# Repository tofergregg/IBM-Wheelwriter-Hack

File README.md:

# IBM-Wheelwriter-Hack
Turning an IBM Wheelwriter into a unique printer

Video:<br>

This project has three goals:

1. Electronically connect an Arduino to an IBM Wheelwriter 6 (will probably work for other models) to emulate the IBM printer option card when using a custom driver.
2. Allow someone to type directly to the typewriter from a computer keyboard, through a computer.
3. Add fun options, e.g., raster printing (!) at a low dpi through the use of micro-up/down and micro-backspace.

## Background
The IBM Wheelwriter, circa 1984, is an electronic typewriter with a beautiful Model M keyboard and a daisy-wheel print head. The typewriter is (not suprisingly, given that it is an IBM) built like a tank, and the PCBs are exceedingly well laid out and annotated, and easy to access. The case pops off with a bit of elbow grease, and there is an expansion port on one of the two PCBs with labeled pins. Yay!

## Technical Details
The only pins we really care about are "bus" and ground, although eventually we'll care about 5V when we attach the Arduino and want to power it from the typewriter itself.

Reverse-engineering the bus has been an interesting two-week endeavor. The tools necessary: an Arduino (I'm using a Light Blue Bean+ (Update on 17 Jan 2017: I have added code for an ATmega Arduino Nano) and a logic analyzer. The initial logic analyzer I used was a Bus Pirate, but unfortunately the BP does not have enough memory to capture some of the longer sequences of commands (e.g., a carriage return). So, a colleague loaned me a Saleae 8-pin logic analyzer, which has worked great (though it does have some quirks).

As of February 2017, I have successfully reverse engineered printing characters, carriage returns, fast printing of characters, print head forwards/backwards/up/down, etc. Here is the basic idea for sending a command on the bus:

* Pulse period: 5.34us (I originally thought it was a 5.25us pulse, but after locating the 11.975MHz crystal on the PCB, I realized that 11.975MHz divided by 64 is 5.34us, which is most likely the actual period. In all of my testing I assumed it was 5.25us, and it worked fine.
* Number of pulses sent per command: 10 (an "I'm writing to the bus" to begin, and nine more bits)
* Normal state of the bus: high (5V), and devices sending commands must pull the bus to low for a zero, and leave high for a one.
* The first pulse is always a throwaway 0, indicating that a device is going to write 9 more bits to the bus.
* The next nine bits are (as far as I can tell) in LSB order. Commands seem to always start with 0b100100001 (which is sent right-most bit first). I originally thought the commands were MSB first, but when I was reverse engineering the carriage-return command the numbers came out such that it looks like it is LSB. This makes reading the logic traces in the reverse order from the numeric bit pattern. Maybe I should have kept the MSB ordering in the code because it is easier for humans to read, but I switched it to make it consistent with the way the typewriter expects commands.
* When a device sends its 10 bits on the bus, there is almost always a response from the motor driver PCB (that's what I'm calling it), and this response is usually a 10-byte zero (a 53.4us zero pulse, basically). We need to look for this response before sending the next 10-bit value in our command.
* The reason I am somewhat hesitant to declare the MSB/LSB debate finished is because the character table is completely whacky. It is not ASCII, and it isn't any of the EBCDIC variations I've tracked down. You might think that there would be some method to it, but I haven't yet figured it out. The table below is what I have so far; as you can see, the characters A, B, C have character codes 0x20, 0x12, and 0x1b. I have a feeling that the codes might be based off of the keyboard scan codes, but I haven't found the pattern yet.

* The following is the Arduino array mapping ASCII to the characters the printer expects.
I haven't figured out what encoding the typewriter expects, and capturing this data was
an exercise in patience and a lot of "type a key, look at the bit pattern" (which I
automated to every extent possible!). Note: this is the mapping for the __Prestige Elite 12P__
daisy wheel -- I will eventually get a Courier printwheel to see what characters need to be
modified (e.g., there are no curly braces in the Prestige Elite font).

<pre>
int asciiTrans[128] = 
//col: 0     1     2     3     4     5     6     7     8     9     a     b     c     d     e     f     row:
    {0x00, 0x00, 0x00, 0x00, 0x00, 0x00, 0x00, 0x00, 0x00, 0x00, 0x00, 0x00, 0x00, 0x00, 0x00, 0x00, // 0

//    
     0x00, 0x00, 0x00, 0x00, 0x00, 0x00, 0x00, 0x00, 0x00, 0x00, 0x00, 0x00, 0x00, 0x00, 0x00, 0x00, // 1
     
//    sp     !     "     #     $     %     &     '     (     )     *     +     ,     -     .     /
     0x00, 0x49, 0x4b, 0x38, 0x37, 0x39, 0x3f, 0x4c, 0x23, 0x16, 0x36, 0x3b, 0xc, 0x0e, 0x57, 0x28, // 2
     
//     0     1     2     3     4     5     6     7     8     9     :     ;     <     =     >     ?
     0x30, 0x2e, 0x2f, 0x2c, 0x32, 0x31, 0x33, 0x35, 0x34, 0x2a ,0x4e, 0x50, 0x00, 0x4d, 0x00, 0x4a, // 3

//     @     A     B     C     D     E     F     G     H     I     J     K     L     M     N     O
     0x3d, 0x20, 0x12, 0x1b, 0x1d, 0x1e, 0x11, 0x0f, 0x14, 0x1F, 0x21, 0x2b, 0x18, 0x24, 0x1a, 0x22, // 4

//     P     Q     R     S     T     U     V     W     X     Y     Z     [     \     ]     ^     _
     0x15, 0x3e, 0x17, 0x19, 0x1c, 0x10, 0x0d, 0x29, 0x2d, 0x26, 0x13, 0x41, 0x00, 0x40, 0x00, 0x4f, // 5
     
//     `     a     b     c     d     e     f     g     h     i     j     k     l     m     n     o
     0x00, 0x01, 0x59, 0x05, 0x07, 0x60, 0x0a, 0x5a, 0x08, 0x5d, 0x56, 0x0b, 0x09, 0x04, 0x02, 0x5f, // 6
     
//     p     q     r     s     t     u     v     w     x     y     z     {     |     }     ~    DEL
     0x5c, 0x52, 0x03, 0x06, 0x5e, 0x5b, 0x53, 0x55, 0x51, 0x58, 0x54, 0x00, 0x00, 0x00, 0x00, 0x00}; // 7
</pre>

To send commands to the typewriter, we connect one pin of the Arduino to the bus through a MOSFET transistor (see the breadboard layout below, or the schematic in the
KiCad files). When we set this pin high, the bus is pulled low, indicating a zero that we want to send. We capture other devices commands with a different Arduino pin that reads the raw state of the bus.

The hardest part about making the commands work is that there isn't a clock on the bus, and all commands must be timed for as close to 5.34us pulses as we can get. The Arduino is *just* barely fast enough to do this, and you have to resort to directly writing to the `PORTD` (or `PORTB`) pin registers and reading from the `PIND` (or `PINB`) registers to hit the tolerances. I.e., you can't use `digitalWrite()` or `digitalRead()` -- the commands are just too slow. The highest granularity timer we have access to on the Arduino (without going super-duper low-level) is `delayMicroseconds()`, which can come close enough to 5.34us to work, but it takes a bit of fiddling to get right. I will eventually port the code to an Arduino proper, but on the Light Blue Bean+, the tolerances don't have any wiggle room. Side note: the LBB+ has some internal ports rearranged, so `PORTD` and `PORTB` do not map to the standard Arduino pins. I've noted that in the code where necessary, and the code for the Arduino Nano has slightly different pins: pin 2 is the bus trigger through the MOSFET, and pin 3 is the bus input. Pin 4 is currently used as a button for testing.  

## Graphics
This has been one of the most fun parts of the project. I realized early on during my analysis of the 
signals coming from the bus that the typewriter has the ability to advance the print head in very small increments,
both horizontally and vertically. This led to the idea that I could basically turn the typewriter 
into a slow, low-resolution dot-matrix printer by utilizing the period key as a pixel, and printing out runs of 
dots and spaces to form images.

My initial attempts involved simply breaking an image down into a grid of black-and-white pixels,
and then sending each black pixel as a period, and each white pixel as a space. This worked, but was
exceedingly slow (as you can imagine). For the second iteration, I re-wrote the encoding algorithm to 
accept a [run-length-encoded](https://en.wikipedia.org/wiki/Run-length_encoding) string of periods and
spaces, allowing me to fast-print the runs, which sped up the process considerbly. In the current
iteration, I have updated the Arduino code to print runs of periods (as before), but also to simply
advance the print head an equivalent number of spaces for whitespace, instead of individually
advancing one space at a time (which sounded cool, but was slow...)

At this point, the graphics printing code on the Arduino is stable, but I'm still trying to
figure out the best way to scale images so they make sense in black and white when
printed at (roughly) 50-dots per inch. As I write more of the front-end software, I imagine
I will re-invent the wheel some more and land on a reasonable method.

Here is an example of what the graphics looks like:

## Bold, underline, and other non-standard functions
Interstingly, the Wheelwriter 6 that I have does not have bold functionality, 
though it does have a built-in underline function. Not suprisingly, an underline
is as simple as writing a character then immediately writing the underline character,
before advancing the print head. I have manually implemented this instead of attempting
to turn on the built-in underline functionality.

Bold is a bit more interesting: because this model does not have a bold function, I
had to play around with what bold should look like. It turns out that the best bold
I have been able to create works like this:

1. print a character
2. advance the print head one micro-space
3. reprint the character
4. advance the print head a full character space less one microspace (to keep the spacing intact).

I think the bold looks great. :)

If anyone has any ideas on how to get the daisy wheel to print at an angle, let
me know so I can implement italics. (/joke)  

For the `sendToNano.py` program, I have included a parser that
looks for "**" (bold) and "__" (underline) Markdown and sends the appropriate commands
to the typewriter to format text in this fashion.

Here is a picture of the output with formatted text:

## Breadboard Layout
The circuit used to connect the typewriter to an Arduino is extremely simple. 

## Nano Shield PCB

See the KiCad files for full schematic ([hardware/Arduino_NanoShield folder](hardware/Arduino_NanoShield)) of a Nano shield,
or order the part directly from OSH Park (under $6 for three copies):

<a href="https://oshpark.com/shared_projects/HWk60tsg"></img></a>

(Note: you will need two surface-mount components for the shield: a 
[200&#8486; 1206 resistor ($0.10 at Digikey)](http://www.digikey.com/product-detail/en/yageo/RC1206JR-07200RL/311-200ERCT-ND/732194)
(and anything in the 200&#8486; range should work), 
and an [n-channel MOSFET (2N7002 works fine) in an SOT-23 package, ($0.14 at Digikey)](http://www.digikey.com/product-detail/en/on-semiconductor/2N7002LT1G/2N7002LT1GOSCT-ND/917791)).
If you want a proper connector for the typewriter interface, [you can get one, too ($0.56 at DigiKey)](https://www.digikey.com/product-detail/en/molex-connector-corporation/0050579310/WM5289-ND/2731451)

Note: you do __not__ need to connect the 5V to the typewriter (indeed, do not, or you risk electrical issues);
I put that onto the board in case someone did not want to connect the Arduino through USB. But, USB is how
the computer controls the typewriter, so it will be connected...

Of course, you also need to be
able to [solder surface mount components](https://www.sparkfun.com/tutorials/category/2).

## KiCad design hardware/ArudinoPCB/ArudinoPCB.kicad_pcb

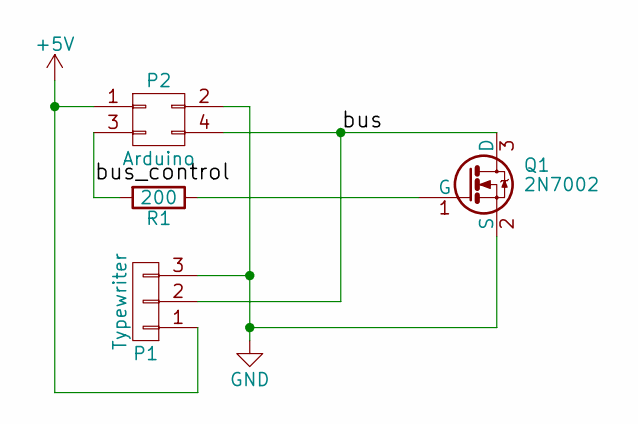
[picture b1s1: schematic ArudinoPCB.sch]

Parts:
P1: Typewriter; Socket_Strip_Straight_1x03
P2: Arduino; Socket_Strip_Straight_2x02
Q1: 2N7002; SOT-23
R1: 200; R_1206

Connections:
+5V: P1.1, P2.1
GND: P1.3, P2.2, Q1.2 (S)
unnamed: P1.2, P2.4, Q1.3 (D)
unnamed: P2.3, R1.2
unnamed: Q1.1 (G), R1.1

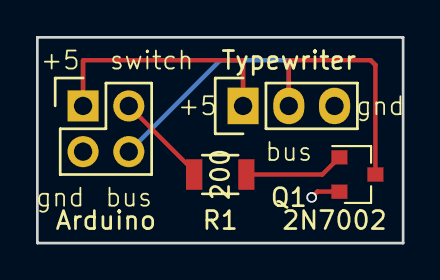
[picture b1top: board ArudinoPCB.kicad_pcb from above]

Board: 2 copper layers, 20.3 x 11.4 mm, 4 parts (0 on the bottom side), 5 nets.

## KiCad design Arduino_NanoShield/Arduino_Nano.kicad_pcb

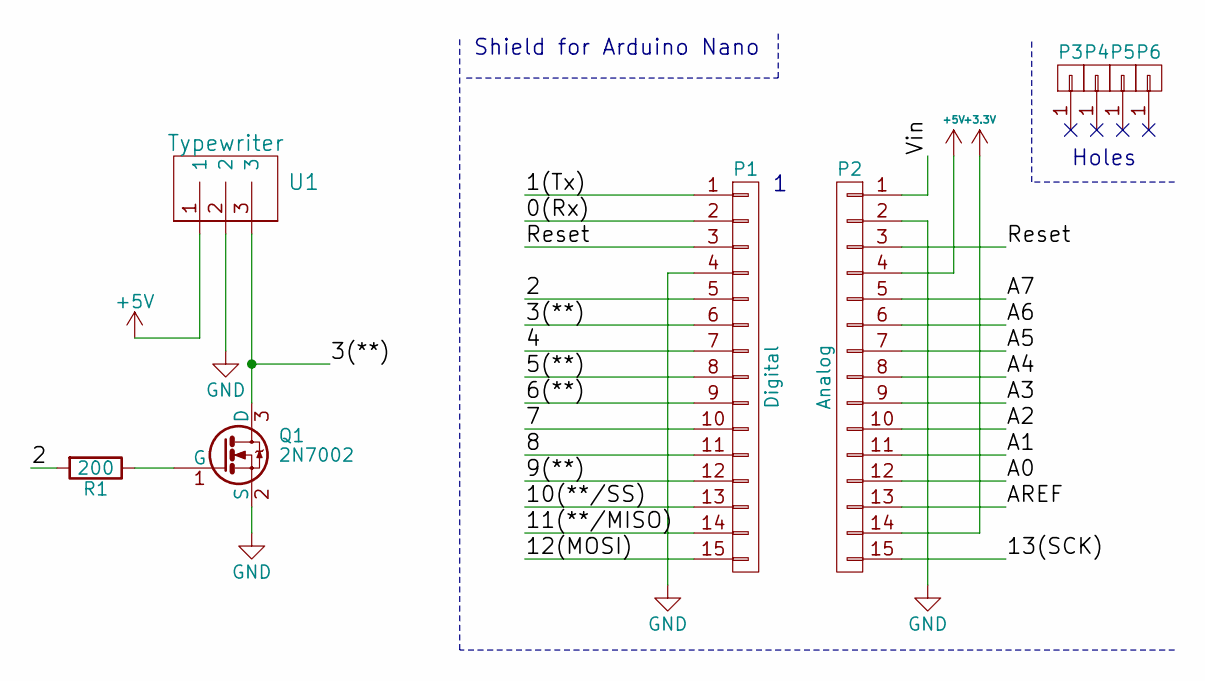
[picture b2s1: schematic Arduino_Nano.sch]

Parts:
P1: Digital; Socket_Strip_Arduino_1x15
P2: Analog; Socket_Strip_Arduino_1x15
P3, P4, P5, P6: CONN_01X01; 1pin_Nano
Q1: 2N7002; SOT-23
R1: 200; R_1206
U1: Typewriter; ph-connectorJST1x3

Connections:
+3V3: P2.14
+5V: P2.4, U1.1
/0(Rx): P1.2
/1(Tx): P1.1
/2: P1.5, R1.2
/3(**): P1.6, Q1.3 (D), U1.3
/4: P1.7
/5(**): P1.8
/6(**): P1.9
/7: P1.10
/8: P1.11
/9(**): P1.12
/10(**/SS): P1.13
/11(**/MISO): P1.14
/12(MOSI): P1.15
/13(SCK): P2.15
/A0: P2.12
/A1: P2.11
/A2: P2.10
/A3: P2.9
/A4: P2.8
/A5: P2.7
/A6: P2.6
/A7: P2.5
/AREF: P2.13
/Reset: P1.3, P2.3
/Vin: P2.1
GND: P1.4, P2.2, Q1.2 (S), U1.2
unnamed: Q1.1 (G), R1.1

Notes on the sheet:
Holes
Shield for Arduino Nano

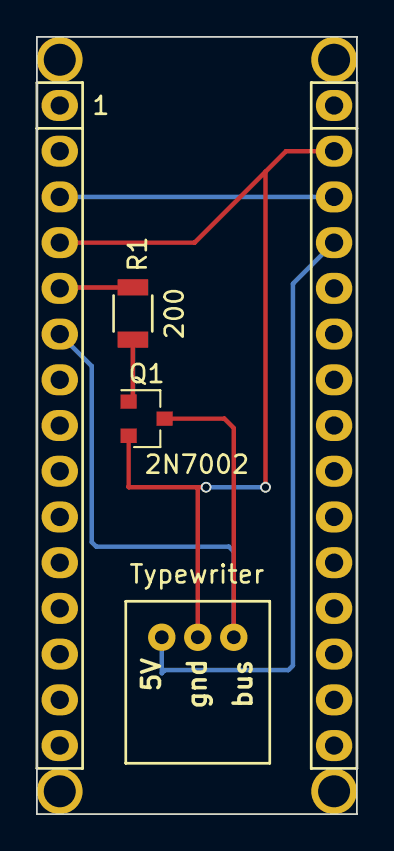
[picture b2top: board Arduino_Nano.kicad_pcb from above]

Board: 2 copper layers, 17.8 x 43.2 mm, 9 parts (0 on the bottom side), 6 nets.

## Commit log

2016-12-16 added blank license
2016-12-16 updated sketch
2016-12-17 non-working controller with interrupt for pin
2016-12-17 non-working controller without interrupt
2016-12-17 working except for return not using interrupts
2016-12-17 working!
2016-12-17 added print_strln() function
2016-12-18 Added text input via serial port and also added textToBean.py file to stream file to typewriter
2016-12-18 added an actual typewriter program
2016-12-18 bean program now prints one character at a time when receiving from serial
2016-12-18 updated .gitignore to ignore files that end with tilde ~
2016-12-18 created curses based actual typewriter, which is better
2016-12-18 added up/down arrow keys for full up/down
2016-12-18 added micro-commands
2016-12-18 updated programs for minor fixes
2016-12-18 more software tweaks
2016-12-19 implemented fast text for up to 20 characters of text
2016-12-20 minor modifications for speed
2016-12-27 testing bean with program that takes less memory
2017-01-01 wheelwriter control before updating to remove queue
2017-01-01 removed queue from program
2017-01-01 updated control program to print up to 60 characters at a time
2017-01-01 updated control app
2017-01-01 Updated control for better serial handling, with the necessity of passing in the file length (max 65kb) and updated textToBean to accomodate this change
2017-01-02 tweaked to work with actualtypewriter program
2017-01-02 added micro-forward-space
2017-01-02 added more space feature and added no-space character
2017-01-02 added a command byte, to allow commands and also to allow straight ascii to be sent one character at a time
2017-01-04 up to date before changing to run-length encoding
2017-01-04 Added sendImage that works moderately well for small images and before run-length encoding
2017-01-04 updated sendImage.py for run-length encoding
2017-01-04 first attempt at run length encoding for images
2017-01-04 run length encoding working for bw images
2017-01-04 updates for run length encoding
2017-01-06 more mods to the image and trying to debug actualTypewriter
2017-01-06 still updating
2017-01-12 Python Cleanup
2017-01-16 Added Arduino Nano code and schematics
2017-01-17 updated nano code
2017-01-20 updated nano printing for graphics
2017-01-20 renamed Nano wheelwriter arduino program
2017-01-24 updated README to indicate a pulse period of 5.34us instead of 5.25us
2017-01-30 updated to work with Linux
2017-01-30 updated for linux and added moog25.png
2017-01-30 updated for Windows
2017-01-31 added bold and underline
2017-01-31 tweaking bold and underline
2017-01-31 updated bold and underline to accept markdown ** and __
2017-01-31 updated port choice to enable a hardcoded port
2017-02-01 sped up graphics a bit
2017-02-01 sped everything up, although I'm not convinced it is a viable modification
2017-02-01 updated demo.sh for Nano
2017-02-04 first attempt at word processor for typewriter, mac os
2017-02-04 added blinkenlight to Nano
2017-02-08 added graphics printing to Mac program. Still working on printing both text and graphics
2017-02-08 added breadboard image and Fritzing file
2017-02-08 updated README to include breadboard
2017-02-08 updated breadboard image
2017-02-08 updated breadboard image and readme
2017-02-09 fixed issue with printing images
2017-02-09 updated README to include a bit on graphics, bold, underline
2017-02-09 added image to readme
2017-02-09 updated README to include an image of formatted text
2017-02-09 removed folder
2017-02-09 re-organized github
2017-02-09 still reorganizing
2017-02-10 Making progress on word processor
2017-02-18 updated demo
2017-02-18 added case images for nano and shield for laser cutting
2017-02-18 working on reverse text
2017-02-18 added quick brown fox text
2018-07-05 updated microspaces
2018-07-05 added spaces program
2018-07-05 updated text with kludgy spacing
2018-07-06 added GIS_Project folder
2018-07-06 reset WheelwriterControlNano.ino to original
2018-07-06 updated GIS naming
2018-07-06 added readme for GIS
2018-07-06 cleaned up textWithSpaces.py
2018-07-06 added horizontal and vertical command to Nano
2018-07-06 updated textWithSpaces to put value in twos complement, and updated arduino sketch to accomodate this
2018-07-06 added resetTypewriter.py and returnCursor.py
2018-07-07 added server and client for continuous serial connection
2018-07-07 updated server and Nano program
2018-07-09 updated client, server, and nano
2018-07-09 moved server client into GIS main folder
2018-07-09 added readme for server and send_command
2018-07-09 updated return to have it move a default of one line spacing
2018-07-09 working on testing
2018-07-09 updated server and arduino to receive and send null terminator
2018-07-09 minor updates
2018-07-09 working version of server
2018-07-10 updated testing and took out some debug statements in server
2018-07-10 updated testMicrospaces
2018-07-11 smoothed out horizontal spacing
2018-07-20 updated server a bit
2018-07-21 took out exit in testLetterSize.sh
2018-07-25 took out EEPROM dependency from sketch
2018-12-20 enforced python 2.7 on server.py and send_command.py
2018-12-20 updated actualTypewriterNano.py to enforce python2.7
2018-12-20 updated scripts to use python 2.7
2019-01-18 added ROM reader files
2019-01-18 added info about decompiling in blake_emails.txt
2019-01-18 added pinout link for raspi
2019-01-29 added printer escape code examples for wheelwriter 10/15 printer option
2019-01-29 added ROM info
2019-01-29 updated wheelwriter 10/15 printer option info
2019-01-30 added linefeed test
2019-04-12 added document sending code
2019-04-14 added voice folder for Nick
2019-04-14 fixed microspacing for bold and underline
2019-04-14 added simple test
2019-04-14 updated texts
2019-04-14 updated nick letter
2019-04-14 updated letter and fixed server issue
2019-04-14 fixed sendDoc.sh to properly send lines that begin with dash
2019-05-23 Add some hex version of binary, add some comments
    From my own reverse engineering, using a Saleae logic analyzer clone with Sigrok's Pulseview and protocol decoding and observing the commands appearing on the bus in response to keyboard presses on a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
    Observations:
    * The protocol is a 9-bit serial, apparently the so-called "mode 2" referred to in the Intel 8051 documentation: http://datasheets.chipdb.org/Intel/MCS51/MANUALS/27238302.PDF
    * The 9-bit bytes with the most-significant bit set indicate that the remaining bits are a processor address intended to listen to the commands that follow, so the many 0x121 are just spamming an ann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
2019-06-05 updated datasheets for ROMS
2019-06-25 added full ROM programmer with read, write, erase for SST39SF010A chip
2019-06-25 updated rom programmer
2019-07-04 updaated rom_programmer
2021-02-22 updated textToNano.py to be Python 3
2021-02-22 updated GIS server and client to use Python3
